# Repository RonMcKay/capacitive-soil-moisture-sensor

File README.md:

<div align="center">

# Capacitive Soil Moisture Sensor

</div>

This is a capacitive soil moisture sensor which runs with a standalone ATmega328P and utilizes the [MySensors][1] framework.
It can however be adapted to any other framework that uses 2.4 GHz radio communication with an NRF24L01 if you upload your own code.

A short summary of the features is:
* Runs on 2 AAA batteries
* Sleeping current of 8uA (approx. 10 years of battery life under optimal conditions)
* Uses an NRF24L01 radio module for communication
* Utilizes an ATSHA204A for secure message signing (optional)
* A sensor value range of approximately 400 (from air to water)
* External 8MHz resonator for better temperature stability than the internal oscillator
* All SMD components (except the NRF24L01 radio) on one side of the pcb
* FTDI and AVR ISP connector for programming and bootloader burning
* 3D printable case

**Note: Take care when inserting the batteries as there is no reverse polarity protection on this board. Also check the pin assignment of the FTDI and AVR ISP headers as these might be non standard to save some space.**

# Table of Contents

- [Getting Started](#getting-started)
    - [Requirements](#requirements)
- [Hardware](#hardware)
    - [PCB Production](#pcb-production)
    - [Assembly](#assembly)
    - [Case](#case)
- [Software](#software)
    - [Calibration](#calibration)
- [Future Improvements](#future-improvements)
- [Contributing](#contributing)
- [License](#license)
- [Special Thanks to](#special-thanks-to)
- [Photos](#photos)

# Getting Started

If you want to work on the repository you just have to run:

    git clone --recurse-submodules https://github.com/RonMcKay/capacitive-soil-moisture-sensor

The PCB design is done in KiCad 6. You are pretty much good to go if you open the project with KiCad.

For programming and burning the bootloader I use [Visual Studio Code](https://code.visualstudio.com/)
together with [PlatformIO](https://platformio.org/) and [MiniCore](https://github.com/MCUdude/MiniCore)
(which is already included in the platform io plugin for vs code).

You can generate production/documentation files and run ERC/DRC tests by running `make` in the root directory. All production files are then placed under the hardware directory. The Makefile utilizes [docker](https://www.docker.com/) containers so you should have docker installed.

## Requirements

When working on the project you need the following installed locally and available in the development environment:

- Docker (for generating documentation and production files)
- KiCad 6 (for working on the PCB)
- Openscad (for generating the case)

# Hardware

## PCB Production

In recent years the DIY PCB industry segment has been growing and thus there are numerous options to quite easily order your boards online for low prices. Just download the Gerber-files from the [release page](https://github.com/RonMcKay/capacitive-soil-moisture-sensor/releases) or clone the repository and generate them yourself by running `make`.

## Assembly

For the assembly of your boards there are currently no SMT assembly files supplied with the release, although there are pick and place files for JLCPCB generated by `make` they are not yet optimized or tested, so use them at your own risk. For manual assembly you can find the BOM attached to the release as well as a nice interactive HTML BOM which eases component placement. You only need to take care that the two battery holders which are closest to the radio module do not touch each other as this would cause a short. To be really safe you can bend them away from each other.

**Note:** The ATSHA204A on the board is an optional component. If you do not want to assemble the board with it, you can leave it away together with the accompanying resistor.

## Case

You can find the STL files for a case attached to the release. If you want to tweak the tolerances for your printer or add additional features like printed on version or venting holes you can edit the `hardware/case/case.scad` file and generate the STLs by yourself by running `make case` in the root directory of the repository. The STL files are then placed under `hardware/case`.

# Software

## Calibration

The minimum (air) and maximum (water) sensor values need to be calibrated. For this, get a glass of water and flash the sensor with `#define CALIBRATION_MODE`. While reading out the log messages of the sensor, note down the sensor values for air and submerged in water. Change `AIR_SENSOR_VALUE` and `WATER_SENSOR_VALUE` accordingly and reflash the sensor after commenting out `#define CALIBRATION_MODE`. Your soil moisture sensor is now ready for operation.

# Future Improvements

Here is a list of possible future improvements that might be worth looking into:

* Make the sensor more compact by using a single AA/AAA battery together with a voltage booster
* Changing out the ATmega328P and the NRF24L01 for an NRF52.
* Some temperature readings of the soil would be awesome, like an SMD thermistor or something similar at the tip of the sensor.

Any contributions are highly welcome and I am happy to discuss remarks in the [github discussion section](https://github.com/RonMcKay/capacitive-soil-moisture-sensor/discussions).

# Contributing

I am happy to discuss and accept improvements on the project. Please make all your pull-requests against `master`. It is also a good idea to discuss your planned changes in the [github discussion section](https://github.com/RonMcKay/capacitive-soil-moisture-sensor/discussions) to avoid unnecessary work.

# License

This project is licensed under the CERN-OHL-P v2

# Special Thanks to

* [MySensors Team][1], which made me start creating my own IoT hardware
* miceuz, for his [long writeup](https://wemakethings.net/2012/09/26/capacitance_measurement/) of how capacitive soil moisture sensing is working
* Ken Shirriff, who's post about the [secrets of arduino PWM](http://www.righto.com/2009/07/secrets-of-arduino-pwm.html) made me understand the topic to a certain extend
* Everyone out there who is producing open source hardware and/or guides explaining the topic, which makes the diy electronics topic more accessible

P.S.: The sensor on the photos is only a prototype where I accidentally soldered some wrong value capacitor and forgot a capacitor for the FTDI connector. These are however already fixed in the pcb design.

# Photos

<div align="center">

[1]: https://www.mysensors.org

</div>

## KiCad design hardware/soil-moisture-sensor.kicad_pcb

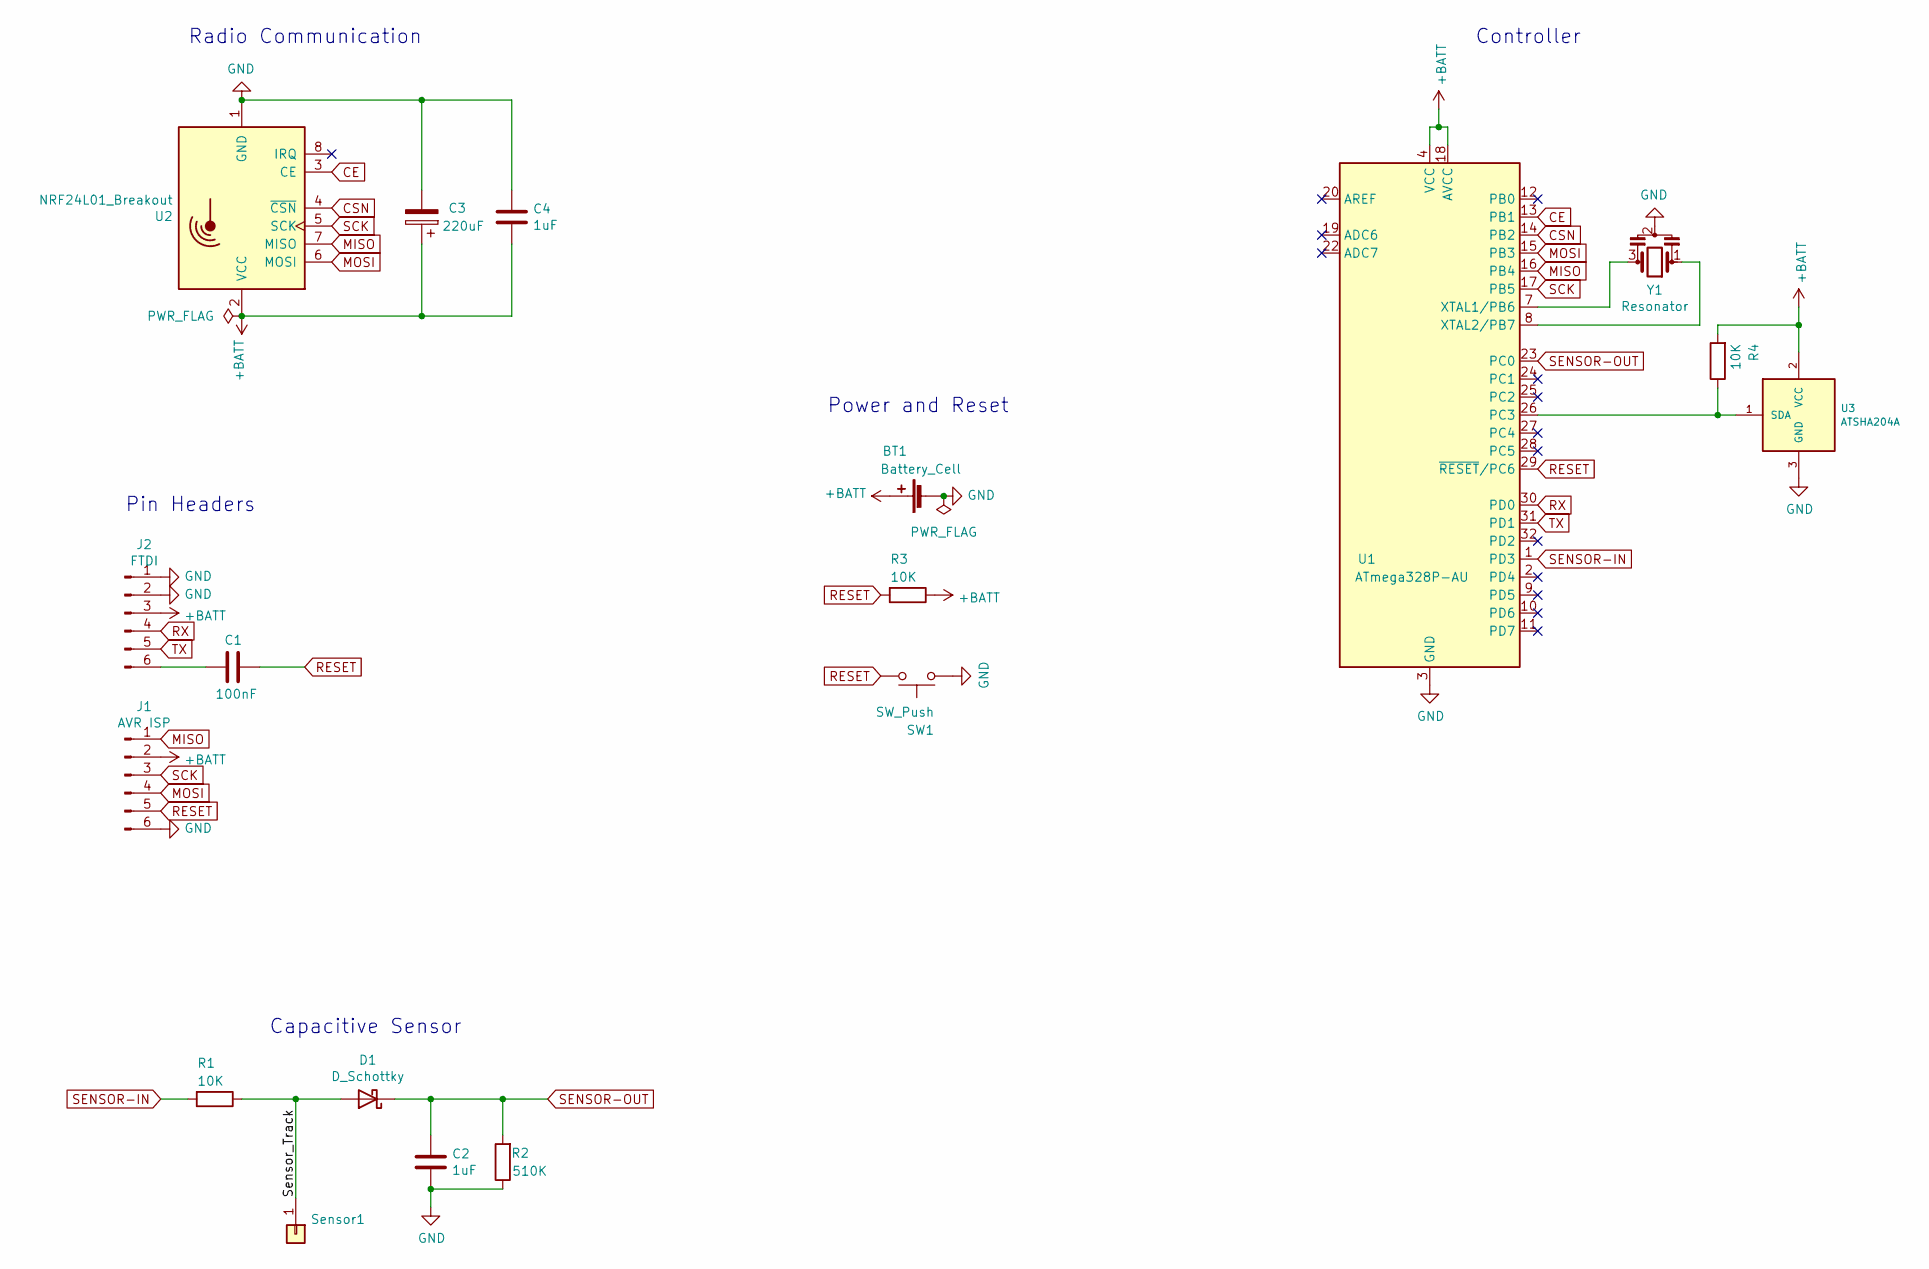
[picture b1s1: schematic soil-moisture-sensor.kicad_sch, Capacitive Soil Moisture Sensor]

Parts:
BT1: Battery_Cell; BatteryHolder_Keystone_597_591_2AAA_3V
C1: 100nF; C_0805_2012Metric_Pad1.15x1.40mm_HandSolder; LCSC C49678
C2, C4: 1uF; C_0805_2012Metric_Pad1.15x1.40mm_HandSolder; LCSC C28323
C3: 220uF; CP_Elec_6.3x7.7; LCSC C127327
D1: D_Schottky; D_SOD-323_HandSoldering; LCSC C154819
J1: AVR ISP; PinHeader_1x06_P2.54mm_Vertical; LCSC C2833331
J2: FTDI; PinHeader_1x06_P2.54mm_Vertical; LCSC C2833331
R1, R3, R4: 10K; R_0805_2012Metric_Pad1.15x1.40mm_HandSolder; LCSC C17414
R2: 510K; R_0805_2012Metric_Pad1.15x1.40mm_HandSolder; LCSC C17733
SW1: SW_Push; Button_2P_TS-1088-AR02016; LCSC C720477
Sensor1: Conn_01x01; Capacitive_Soil_Moisture_Sensor
U1: ATmega328P-AU; TQFP-32_7x7mm_P0.8mm; LCSC C14877
U2: NRF24L01_Breakout; NRF24L01-SMD
U3: ATSHA204A; SOT-23_Handsoldering; LCSC C34377
Y1: Resonator; ceramik_resonator_murata_CSTCE8M00G52-R0; LCSC C907975

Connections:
+BATT: BT1.1 (+), C3.1, C4.2, J1.2, J2.3, R3.1, R4.2, U1.4 (VCC), U1.6 (VCC), U1.18 (AVCC), U2.2 (VCC), U3.2 (VCC)
/Sensor_Track: D1.2 (A), R1.1, Sensor1.1
CE: U1.13 (PB1), U2.3 (CE)
CSN: U1.14 (PB2), U2.4 (~CSN)
GND: BT1.2 (-), C2.2, C3.2, C4.1, J1.6, J2.1, J2.2, R2.1, SW1.1, U1.3 (GND), U1.5 (GND), U1.21 (GND), U2.1 (GND), U3.3 (GND), Y1.2
MISO: J1.1, U1.16 (PB4), U2.7 (MISO)
MOSI: J1.4, U1.15 (PB3), U2.6 (MOSI)
unnamed: C1.2, J2.6
unnamed: R4.1, U1.26 (PC3), U3.1 (SDA)
unnamed: U1.7 (XTAL1/PB6), Y1.3
unnamed: U1.8 (XTAL2/PB7), Y1.1
RESET: C1.1, J1.5, R3.2, SW1.2, U1.29 (~RESET/PC6)
RX: J2.4, U1.30 (PD0)
SCK: J1.3, U1.17 (PB5), U2.5 (SCK)
SENSOR-IN: R1.2, U1.1 (PD3)
SENSOR-OUT: C2.1, D1.1 (K), R2.2, U1.23 (PC0)
TX: J2.5, U1.31 (PD1)

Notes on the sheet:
Capacitive Sensor
Power and Reset
Controller
Radio Communication
Pin Headers

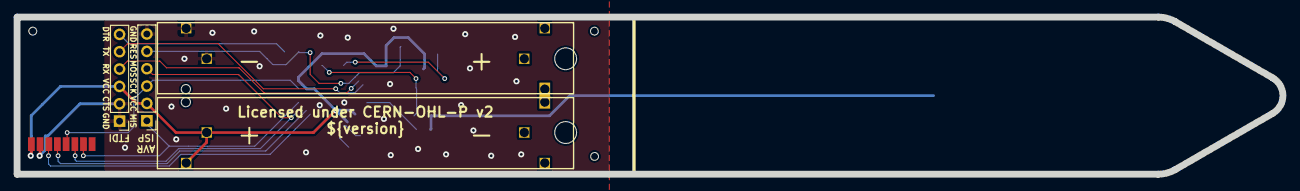
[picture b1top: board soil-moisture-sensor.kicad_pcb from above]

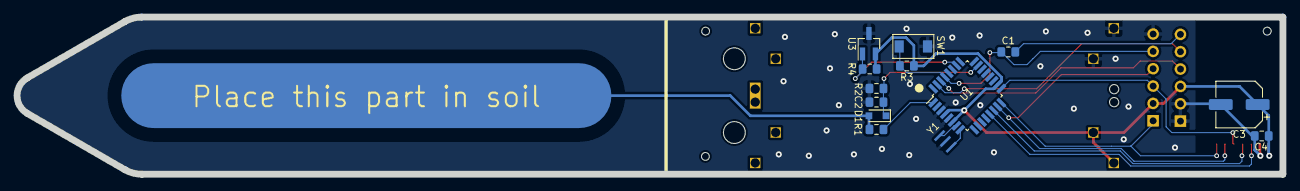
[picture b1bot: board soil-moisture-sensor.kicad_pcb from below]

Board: 2 copper layers, 185.3 x 23.0 mm, 18 parts (14 on the bottom side), 17 nets.

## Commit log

2021-03-12 Add PCB render images
2021-08-13 Add battery runtime estimation
2021-08-19 Improve thread model of case
    Larger threads for easier printing and shorter screw on.
2021-10-30 Add some missing LCSC part numbers and datasheets
2021-10-30 Add BOM
2021-10-31 Add production files for v1.0.0 release
2021-10-31 Add version number to silkscreen
2021-10-31 Make foldernames lowercase
2021-10-31 Move bom to production folder
2021-10-31 Update .gitignore with production files
2021-10-31 Add README for production
2021-10-31 Update BOM with version number
2021-10-31 Remove derived production files of release v1.0.0
2021-12-01 Add CALIBRATION_MODE
    MY_DEBUG should be kept seperate from the calibration of the sensor.
    With the previous setup it was not possible to specify MY_DEBUG to debug
    the wireless transmisison of the sensor as the debug statements were never
    reached.
2021-12-01 Add documentation for calibration of the sensor
2021-12-01 Restrict version to major.minor on the PCB
    Also included the CERN-OHL-P v2 on the schematic.
2021-12-01 Update header levels in README
2022-03-07 Remove some unneccesary info from .pro and .sch
2022-03-07 Add KiCad cache lib
2022-03-07 Fix wrong LCSC part number
2022-03-07 Update footprint of NRF24L01-SMD
2022-03-07 Add config with "rotated" tag
    The +rotated tag will be used for selecting the right components when
    generating the JLCPCB pick and place files.
2022-03-07 Add Makefile
2022-03-07 Change line endings from CRLF to LF
2022-03-07 Update courtyard of NRF24L01 footprint
    The courtyard was not a closed shape which caused DRC errors.
2022-03-07 Add ERC and DRC tests to Makefile
2022-03-09 Add DRC and ERC log files to .gitignore
2022-03-10 Add KiBot config files
2022-03-10 Make tooling holes virtual components
2022-03-10 Update Makefile and README
2022-03-11 Add %%version%% and %%date%% placeholders
    The '%%version%%' and '%%date%%' placeholders have been added to the
    appropriate locations in the schematic and pcb file. They are
    automatically replaced during a release with the correct version and
    date of the release.
2022-03-11 Update .kibot files and Makefile
2022-03-11 Add release workflow
2022-03-15 Add workflow config for review files
2022-03-15 Restrict version to 'major.minor' in GH Workflows
2022-04-16 Update Makefile
2022-04-16 Update replacement of version number in GH WF
2022-04-16 Add option to specify date for review files
2022-04-16 Fix if conditions in GH workflows
2022-06-12 Add possibility to add a version number
2022-06-12 Add venting hole option and organize variables
2022-06-12 Add case to Makefile
2022-06-12 Add stl files to .gitignore
2022-06-12 Add first version of openscad case
2022-06-12 Fix height of shell
2022-06-12 Remove old case stls
2022-06-12 Add interlocking edge
2022-06-12 Integrate generation of case STLs into GH-WF
2022-06-12 Update photos with new case
2022-06-12 Compact OpenSCAD case (#9)
    * Remove old case stls
    * Add stl files to .gitignore
    * Add first version of openscad case
    * Add case to Makefile
    * Add possibility to add a version number
    * Add interlocking edge
2022-06-14 Add header image to README
2022-06-14 Add header image to the README (#10)
2022-10-20 Rename CHANGES.TXT to CHANGELOG.md
    Also updated the format.
2022-10-20 Update CHANGELOG
2022-11-01 build: Add pre-commit and commitizen config
2022-11-01 docs: Update changelog format
2023-01-04 docs(README): Add TOC and state that ATSHA is optional
2023-01-21 Update issue templates
2023-01-22 docs(README): Fix typo
2023-01-22 build(Makefile): Update docker targets
2023-01-22 build(KiBot): Add preflight variable replacement
2023-01-22 build(Makefile): Remove verbose flag from docker target
2023-01-24 build(CI/CD): Update comment in workflow file
2023-01-26 refactor(KiCad)!: Switch to KiCad 6 file layout
2023-01-26 fix(PCB): Remove micro tracks
    From the migration to KiCad 6 there were micro tracks producing errors in the
    DRC.
2023-01-26 build(gitignore): Ignore kicad_pro backup files
2023-01-26 build: Switch to KiCad 6 text variables
2023-01-26 build: Use `restore_project` setting instead of copying source files
2023-01-26 fix: Fix some ERC/DRC warnings
2023-01-26 docs(README): Update README
2023-01-26 ci(CI/CD): Change to KiCad 6 action of KiBot for GH workflows
2023-01-27 docs(CHANGELOG): Update changelog
2023-01-27 Switch PCB Project to Kicad 6 (#13)
    * refactor(KiCad)!: Switch to KiCad 6 file layout
    * fix(PCB): Remove micro tracks
    From the migration to KiCad 6 there were micro tracks producing errors in the
    DRC.
    * build(gitignore): Ignore kicad_pro backup files
    * build: Switch to KiCad 6 text variables
2023-01-29 Create release workflow
2023-01-29 Add commit and release tasks
2023-02-03 Add generation of release assets to `release.yml`
2023-02-03 Create automatic release workflow (#14)
    * Create release workflow
    * Add commit and release tasks
    * Add generation of release assets to `release.yml`
2023-02-03 ci(BOM): Include LCSC part numbers into ibom
2023-02-03 Add LCSC part numbers to iBOM (#15)
    ci(BOM): Include LCSC part numbers into ibom
2023-02-03 build: Generate top and bottom view in png format
2023-02-04 docs: Update header image with PCB top/bottom render
2023-02-04 docs(README): Add version badge to README
2023-02-04 ci: Automatically generate new README header images on release
2023-02-04 ci: Use GITHUB_TOKEN to generate the changelog
2023-02-04 Automatically update the README header images on new release (#16)
    * build: Generate top and bottom view in png format
    * docs: Update header image with PCB top/bottom render
    * docs(README): Add version badge to README
    * ci: Automatically generate new README header images on release
    * ci: Use GITHUB_TOKEN to generate the changelog
2023-02-05 ci: Include tracks and zones into the iBOM
2023-02-05 Include tracks and zones into the iBOM (#17)
    ci: Include tracks and zones into the iBOM
2023-02-05 ci: Switch to master only setup
2023-02-05 Switch to master only setup (#18)
    ci: Switch to master only setup
2023-02-05 ci: Change default name for release branches
2023-02-05 Change default name for release branches (#19)
    ci: Change default name for release branches
2023-02-06 docs(README): fix some typos
2023-02-17 Fix branch for release workflow
2023-02-17 Update CHANGELOG headings
2023-02-17 Add steps for automatic SemVer increment detection
2023-10-06 ci(release.yml): Update release workflow
2023-10-21 Update release workflow (#24)
    ci(release.yml): Update release workflow
2023-11-26 Add workflow for generating changelog for review
    This way you can generate the changelog and review it before actually
    triggering the workflow for a proper release.
2023-11-26 Add workflow for generating changelog for review (#25)
    This way you can generate the changelog and review it before actually
    triggering the workflow for a proper release.
2023-11-26 Upload whole changelog rather than incremental part
2023-11-26 Upload whole changelog rather than incremental part (#26)

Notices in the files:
hardware/soil-moisture-sensor.kicad_pcb:
Licensed under CERN-OHL-P v2
